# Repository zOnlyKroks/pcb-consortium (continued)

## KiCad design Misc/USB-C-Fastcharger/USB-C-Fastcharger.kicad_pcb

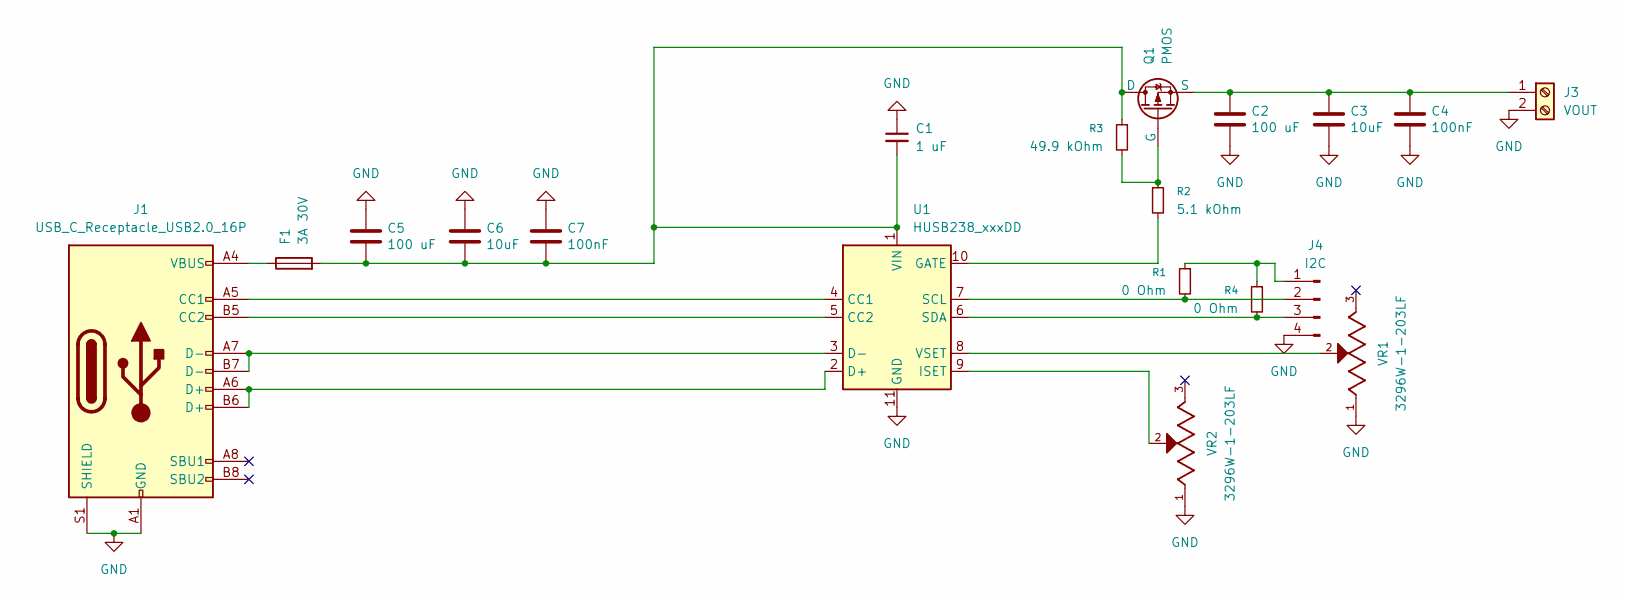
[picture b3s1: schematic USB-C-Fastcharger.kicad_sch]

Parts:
C1: 1 uF; C_0805_2012Metric; LCSC Part # C28323
C2, C5: 100 uF; C_0805_2012Metric; LCSC C141660
C3, C6: 10uF; C_0805_2012Metric; LCSC C440198
C4, C7: 100nF; C_0805_2012Metric; LCSC C49678
F1: 3A 30V; Fuse_2920_7451Metric; LCSC Part # C7190311
J1: USB_C_Receptacle_USB2.0_16P; USB_C_Receptacle_HRO_TYPE-C-31-M-12
J3: VOUT; WJ500V-5.08-2P; LCSC Part # C8465
J4: I2C; PinHeader_1x04_P2.54mm_Vertical; LCSC Part # C2691448
Q1: PMOS; SOT-23; LCSC Part # C150724
R1, R4: 0 Ohm; R_0805_2012Metric; LCSC Part # C17477
R2: 5.1 kOhm; R_0805_2012Metric; LCSC Part # C27834
R3: 49.9 kOhm; R_0805_2012Metric; LCSC Part # C5123618
U1: HUSB238_xxxDD; WDFN-10-1EP_3x3mm_P0.5mm_EP1.8x2.5mm
VR1, VR2: 3296W-1-203LF; TRIM_3296W-1-103LF; PARTREV 05/16; LCSC Part # C49190459

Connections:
GND: C1.1, C2.2, C3.2, C4.2, C5.1, C6.1, C7.1, J1.A1 (GND), J1.A12 (GND), J1.B1 (GND), J1.B12 (GND), J1.S1 (SHIELD), J3.2, J4.4, U1.11 (GND), VR1.1, VR2.1
unnamed: F1.1, J1.A4 (VBUS), J1.A9 (VBUS), J1.B4 (VBUS), J1.B9 (VBUS)
unnamed: J1.A5 (CC1), U1.4 (CC1)
unnamed: J1.B5 (CC2), U1.5 (CC2)
unnamed: C2.1, C3.1, C4.1, J3.1, Q1.3 (S)
unnamed: J4.1, R1.1, R4.1
unnamed: J4.2, R1.2, U1.7 (SCL)
unnamed: J4.3, R4.2, U1.6 (SDA)
unnamed: C1.2, C5.2, C6.2, C7.2, F1.2, Q1.1 (D), R3.1, U1.1 (VIN)
unnamed: Q1.2 (G), R2.1, R3.2
unnamed: J1.A6 (D+), J1.B6 (D+), U1.2 (D+)
unnamed: J1.A7 (D-), J1.B7 (D-), U1.3 (D-)
unnamed: R2.2, U1.10 (GATE)
unnamed: U1.9 (ISET), VR2.2
unnamed: U1.8 (VSET), VR1.2

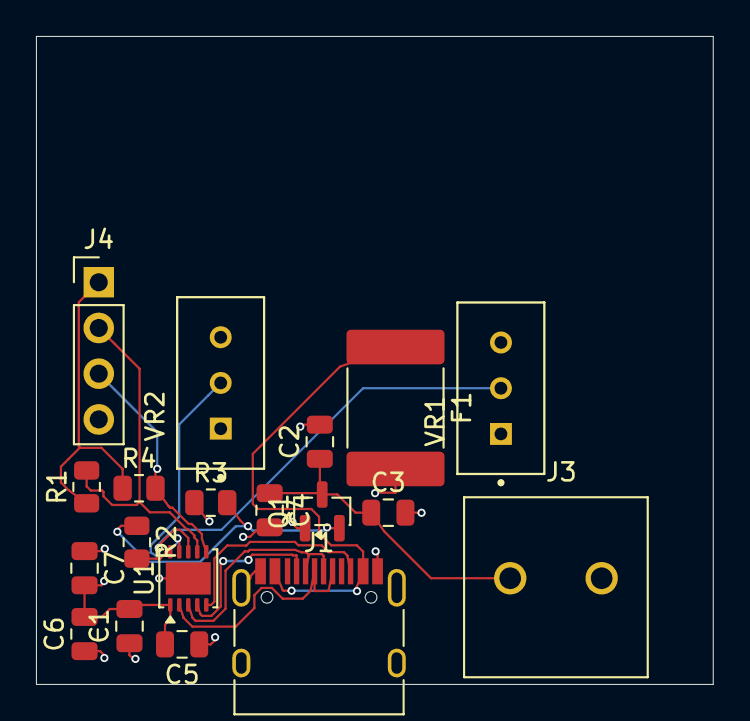
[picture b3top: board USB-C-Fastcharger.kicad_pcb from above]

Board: 4 copper layers, 37.6 x 36.0 mm, 19 parts (0 on the bottom side), 15 nets.

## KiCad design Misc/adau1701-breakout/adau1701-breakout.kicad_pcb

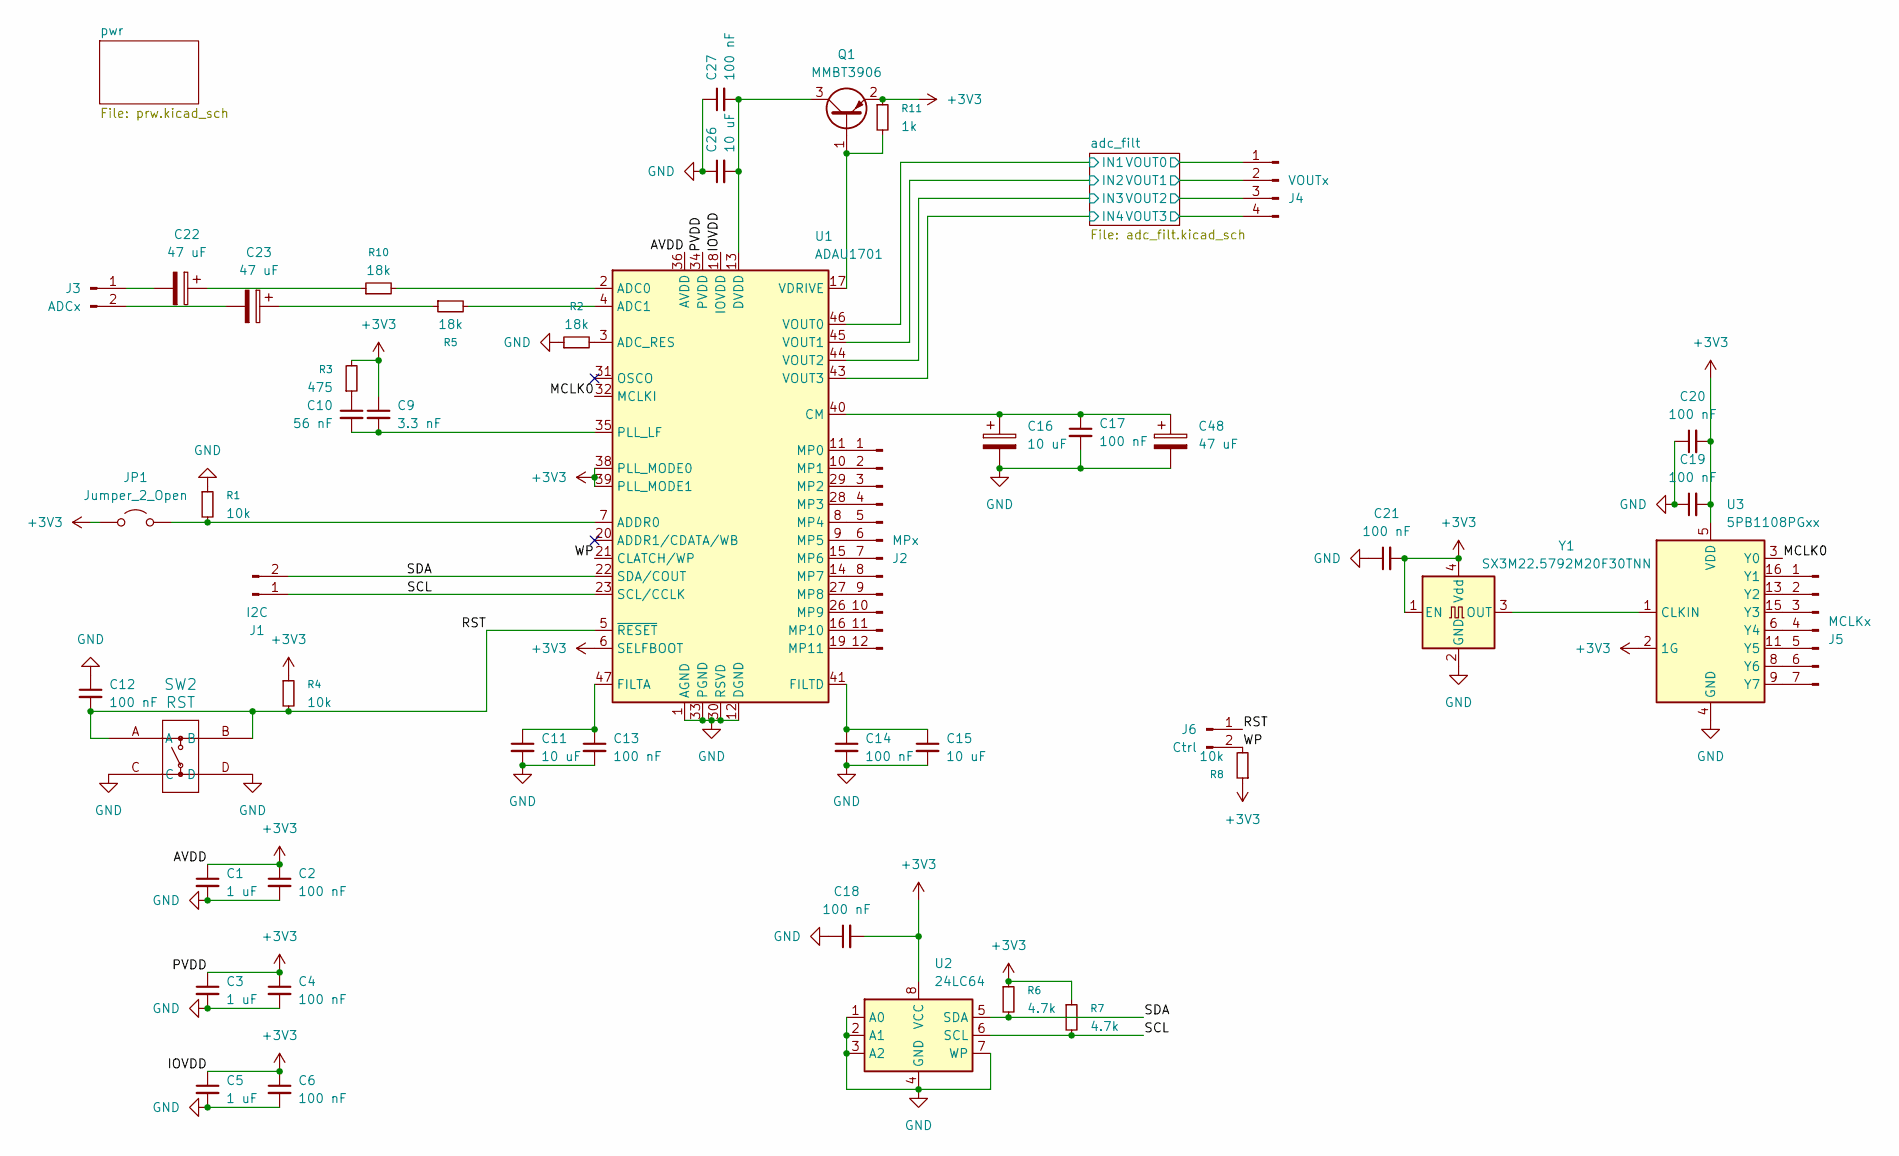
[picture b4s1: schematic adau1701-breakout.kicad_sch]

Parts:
C1, C3, C5: 1 uF; C_0603_1608Metric
C2, C4, C6, C12, C13, C14, C17, C18, C19, C20, C21, C27: 100 nF; C_0603_1608Metric
C9: 3.3 nF; C_0603_1608Metric
C10: 56 nF; C_0603_1608Metric
C11, C15, C16, C26: 10 uF; C_0603_1608Metric
C22, C23, C48: 47 uF; CP_Elec_6.3x5.4
J1: I2C; PinHeader_1x02_P2.54mm_Vertical
J2: MPx; PinHeader_1x12_P2.54mm_Vertical
J3: ADCx; PinHeader_1x02_P2.54mm_Vertical
J4: VOUTx; PinHeader_1x04_P2.54mm_Vertical
J5: MCLKx; PinHeader_1x07_P2.54mm_Vertical
J6: Ctrl; PinHeader_1x02_P2.54mm_Vertical
JP1: Jumper_2_Open; SolderJumper-2_P1.3mm_Open_RoundedPad1.0x1.5mm
Q1: MMBT3906; SOT-23
R1, R4, R8: 10k; R_0603_1608Metric
R2, R5, R10: 18k; R_0603_1608Metric
R3: 475; R_0603_1608Metric
R6, R7: 4.7k; R_0603_1608Metric
R11: 1k; R_0603_1608Metric
SW2: RST; KH-6X6X5H-STM_SKE
U1: ADAU1701; LQFP-48_7x7mm_P0.5mm
U2: 24LC64; SOIC-8_3.9x4.9mm_P1.27mm
U3: 5PB1108PGxx; TSSOP-16_4.4x5mm_P0.65mm
Y1: SX3M22.5792M20F30TNN; Crystal_SMD_3225-4Pin_3.2x2.5mm

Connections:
+3V3: C1.1, C2.1, C3.1, C4.1, C5.1, C6.1, C9.1, C18.2, C19.2, C20.2, C21.2, JP1.1 (A), Q1.2 (E), R3.2, R4.1, R6.1, R7.1, R8.1, R11.1, U1.6 (SELFBOOT), U1.18 (IOVDD), U1.34 (PVDD), U1.36 (AVDD), U1.38 (PLL_MODE0), U1.39 (PLL_MODE1), U1.48 (AVDD), U2.8 (VCC), U3.2 (1G), U3.5 (VDD), U3.10 (VDD), U3.14 (VDD), Y1.1 (EN), Y1.4 (Vdd); also elsewhere on the board
/MCLK0: U1.32 (MCLKI), U3.3 (Y0)
/RST: C12.2, J6.1, R4.2, SW2.A, SW2.B, U1.5 (~RESET)
/SCL: J1.1, R7.2, U1.23 (SCL/CCLK), U2.6 (SCL)
/SDA: J1.2, R6.2, U1.22 (SDA/COUT), U2.5 (SDA)
/WP: J6.2, R8.2, U1.21 (CLATCH/WP)
/adc_filt/IN1: U1.46 (VOUT0); also elsewhere on the board
/adc_filt/IN2: U1.45 (VOUT1); also elsewhere on the board
/adc_filt/IN3: U1.44 (VOUT2); also elsewhere on the board
/adc_filt/IN4: U1.43 (VOUT3); also elsewhere on the board
/adc_filt/VOUT0: J4.1; also elsewhere on the board
/adc_filt/VOUT1: J4.2; also elsewhere on the board
/adc_filt/VOUT2: J4.3; also elsewhere on the board
/adc_filt/VOUT3: J4.4; also elsewhere on the board
GND: C1.2, C2.2, C3.2, C4.2, C5.2, C6.2, C11.2, C12.1, C13.2, C14.2, C15.2, C16.2, C17.2, C18.1, C19.1, C20.1, C21.1, C26.1, C27.1, C48.2, R1.1, R2.1, SW2.C, SW2.D, U1.1 (AGND), U1.12 (DGND), U1.25 (DGND), U1.30 (RSVD), U1.33 (PGND), U1.37 (AGND), U1.42 (AGND), U2.1 (A0), U2.2 (A1), U2.3 (A2), U2.4 (GND), U2.7 (WP), U3.4 (GND), U3.7 (GND), U3.12 (GND), Y1.2 (GND); also elsewhere on the board
unnamed: C10.1, R3.1
unnamed: C22.1, R10.1
unnamed: C23.1, R5.1
unnamed: J2.1, U1.11 (MP0)
unnamed: J2.2, U1.10 (MP1)
unnamed: J2.3, U1.29 (MP2)
unnamed: J2.4, U1.28 (MP3)
unnamed: J2.5, U1.8 (MP4)
unnamed: J2.6, U1.9 (MP5)
unnamed: J2.7, U1.15 (MP6)
unnamed: J2.8, U1.14 (MP7)
unnamed: J2.9, U1.27 (MP8)
unnamed: J2.10, U1.26 (MP9)
unnamed: J2.11, U1.16 (MP10)
unnamed: J2.12, U1.19 (MP11)
unnamed: C22.2, J3.1
unnamed: C23.2, J3.2
unnamed: J5.1, U3.16 (Y1)
unnamed: J5.2, U3.13 (Y2)
unnamed: J5.3, U3.15 (Y3)
unnamed: J5.4, U3.6 (Y4)
unnamed: J5.5, U3.11 (Y5)
unnamed: J5.6, U3.8 (Y6)
unnamed: J5.7, U3.9 (Y7)
unnamed: JP1.2 (B), R1.2, U1.7 (ADDR0)
unnamed: Q1.1 (B), R11.2, U1.17 (VDRIVE)
unnamed: C26.2, C27.2, Q1.3 (C), U1.13 (DVDD), U1.24 (DVDD)
unnamed: R10.2, U1.2 (ADC0)
unnamed: R5.2, U1.4 (ADC1)
unnamed: R2.2, U1.3 (ADC_RES)
unnamed: C16.1, C17.1, C48.1, U1.40 (CM)
unnamed: C11.1, C13.1, U1.47 (FILTA)
unnamed: C14.1, C15.1, U1.41 (FILTD)
unnamed: C9.2, C10.2, U1.35 (PLL_LF)
unnamed: U3.1 (CLKIN), Y1.3 (OUT)

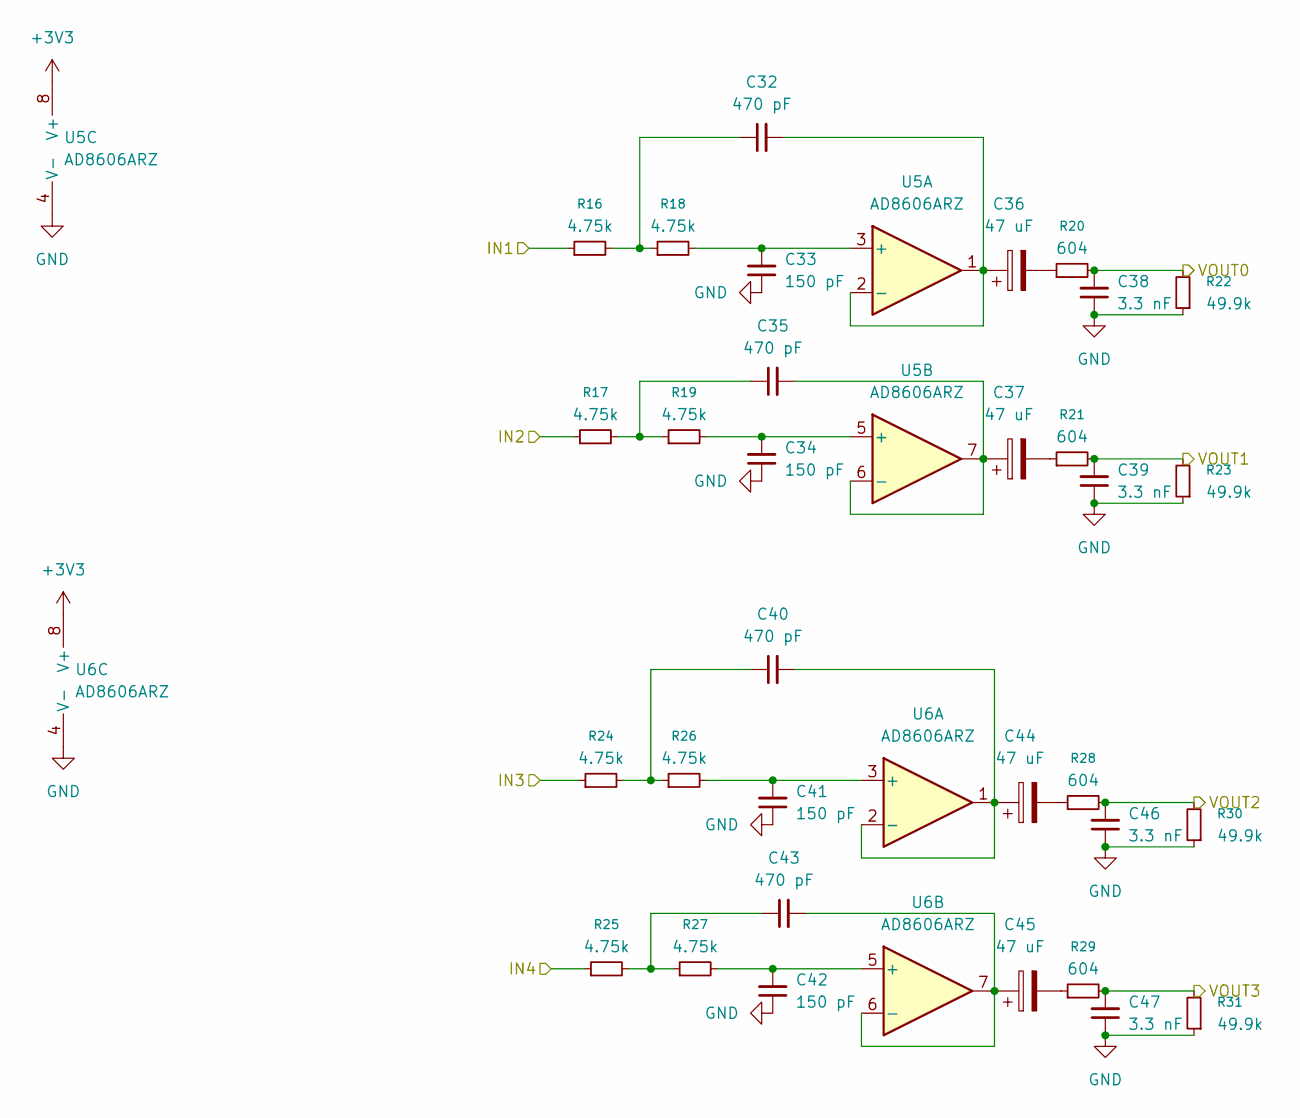
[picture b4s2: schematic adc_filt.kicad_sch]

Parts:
C32, C35, C40, C43: 470 pF; C_0603_1608Metric
C33, C34, C41, C42: 150 pF; C_0603_1608Metric
C36, C37, C44, C45: 47 uF; CP_Elec_6.3x5.4
C38, C39, C46, C47: 3.3 nF; C_0603_1608Metric
R16, R17, R18, R19, R24, R25, R26, R27: 4.75k; R_0603_1608Metric
R20, R21, R28, R29: 604; R_0603_1608Metric
R22, R23, R30, R31: 49.9k; R_0603_1608Metric
U5, U6: AD8606ARZ; SOIC-8_3.9x4.9mm_P1.27mm

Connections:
+3V3: U5.8 (V+), U6.8 (V+); also elsewhere on the board
/adc_filt/IN1: R16.1; also elsewhere on the board
/adc_filt/IN2: R17.1; also elsewhere on the board
/adc_filt/IN3: R24.1; also elsewhere on the board
/adc_filt/IN4: R25.1; also elsewhere on the board
/adc_filt/VOUT0: C38.2, R20.2, R22.2; also elsewhere on the board
/adc_filt/VOUT1: C39.2, R21.2, R23.2; also elsewhere on the board
/adc_filt/VOUT2: C46.2, R28.2, R30.2; also elsewhere on the board
/adc_filt/VOUT3: C47.2, R29.2, R31.2; also elsewhere on the board
GND: C33.1, C34.1, C38.1, C39.1, C41.1, C42.1, C46.1, C47.1, R22.1, R23.1, R30.1, R31.1, U5.4 (V-), U6.4 (V-); also elsewhere on the board
unnamed: C32.1, R16.2, R18.1
unnamed: C35.1, R17.2, R19.1
unnamed: C36.2, R20.1
unnamed: C37.2, R21.1
unnamed: C40.1, R24.2, R26.1
unnamed: C43.1, R25.2, R27.1
unnamed: C44.2, R28.1
unnamed: C45.2, R29.1
unnamed: C33.2, R18.2, U5.3 (+)
unnamed: C32.2, C36.1, U5.1, U5.2 (-)
unnamed: C34.2, R19.2, U5.5 (+)
unnamed: C35.2, C37.1, U5.6 (-), U5.7
unnamed: C41.2, R26.2, U6.3 (+)
unnamed: C40.2, C44.1, U6.1, U6.2 (-)
unnamed: C42.2, R27.2, U6.5 (+)
unnamed: C43.2, C45.1, U6.6 (-), U6.7

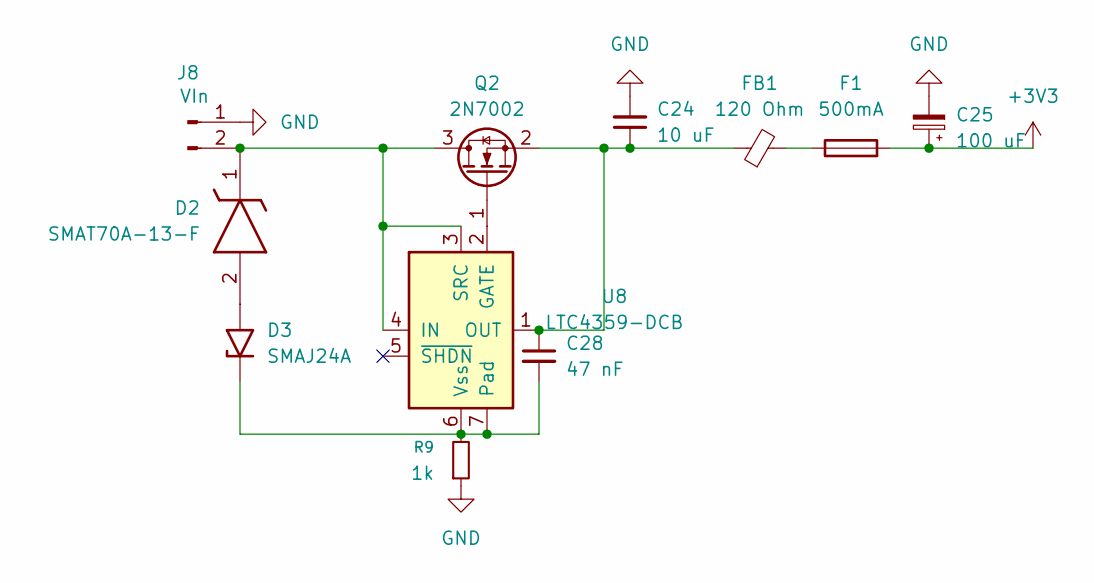
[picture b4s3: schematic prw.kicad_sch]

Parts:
C24: 10 uF; C_0805_2012Metric
C25: 100 uF; CP_EIA-3216-18_Kemet-A
C28: 47 nF; C_0603_1608Metric
D2: SMAT70A-13-F; DIOM5226X230N; Mouser Part Number 621-SMAT70A-13-F
D3: SMAJ24A; D_SMA
F1: 500mA; Fuse_0805_2012Metric
FB1: 120 Ohm; R_0402_1005Metric
J8: VIn; PinHeader_1x02_P2.54mm_Vertical
Q2: 2N7002; SOT-23
R9: 1k; R_0603_1608Metric
U8: LTC4359-DCB; DFN-6-1EP_3x2mm_P0.5mm_EP1.65x1.35mm

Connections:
+3V3: C25.1, F1.2; also elsewhere on the board
GND: C24.2, C25.2, J8.1, R9.1; also elsewhere on the board
unnamed: D2.2 (A), D3.2 (A2)
unnamed: D2.1 (K), J8.2, Q2.3 (D), U8.3 (SRC), U8.4 (IN)
unnamed: C28.2, D3.1 (A1), R9.2, U8.6 (Vss), U8.7 (Pad)
unnamed: F1.1, FB1.2
unnamed: Q2.1 (G), U8.2 (GATE)
unnamed: C24.1, C28.1, FB1.1, Q2.2 (S), U8.1 (OUT)

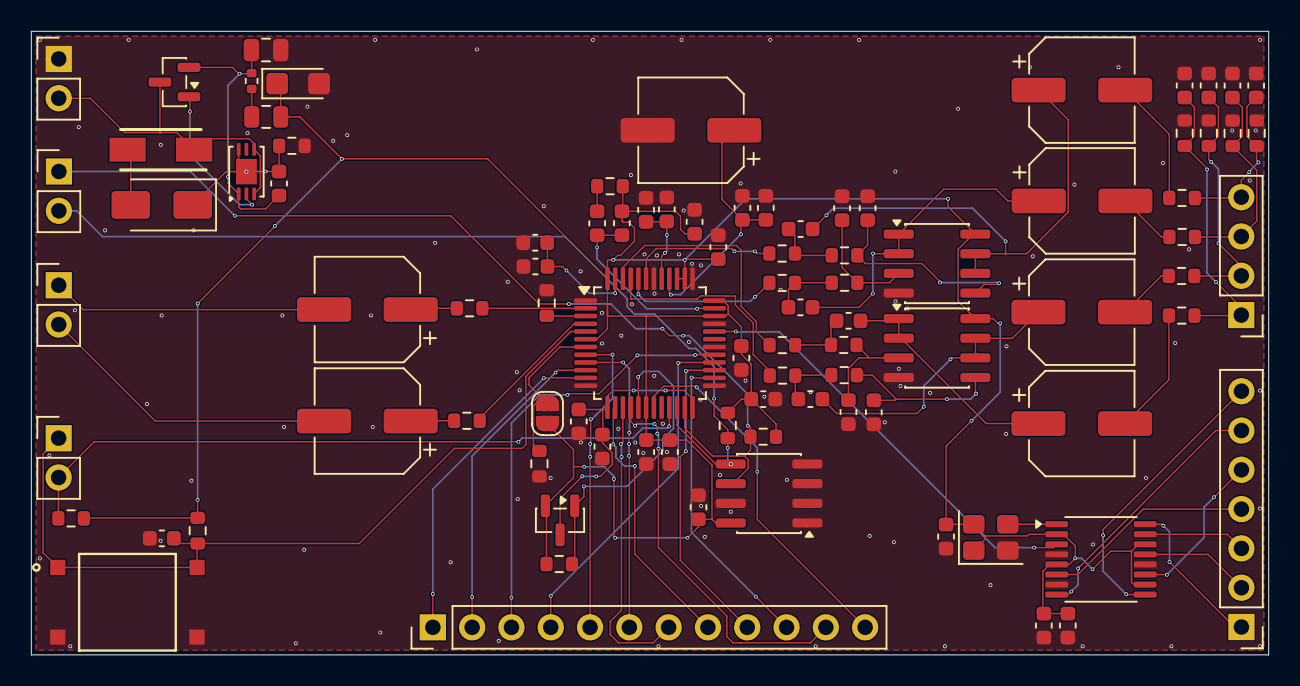
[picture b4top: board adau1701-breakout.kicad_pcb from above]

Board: 2 copper layers, 80.0 x 40.3 mm, 92 parts (0 on the bottom side), 72 nets.

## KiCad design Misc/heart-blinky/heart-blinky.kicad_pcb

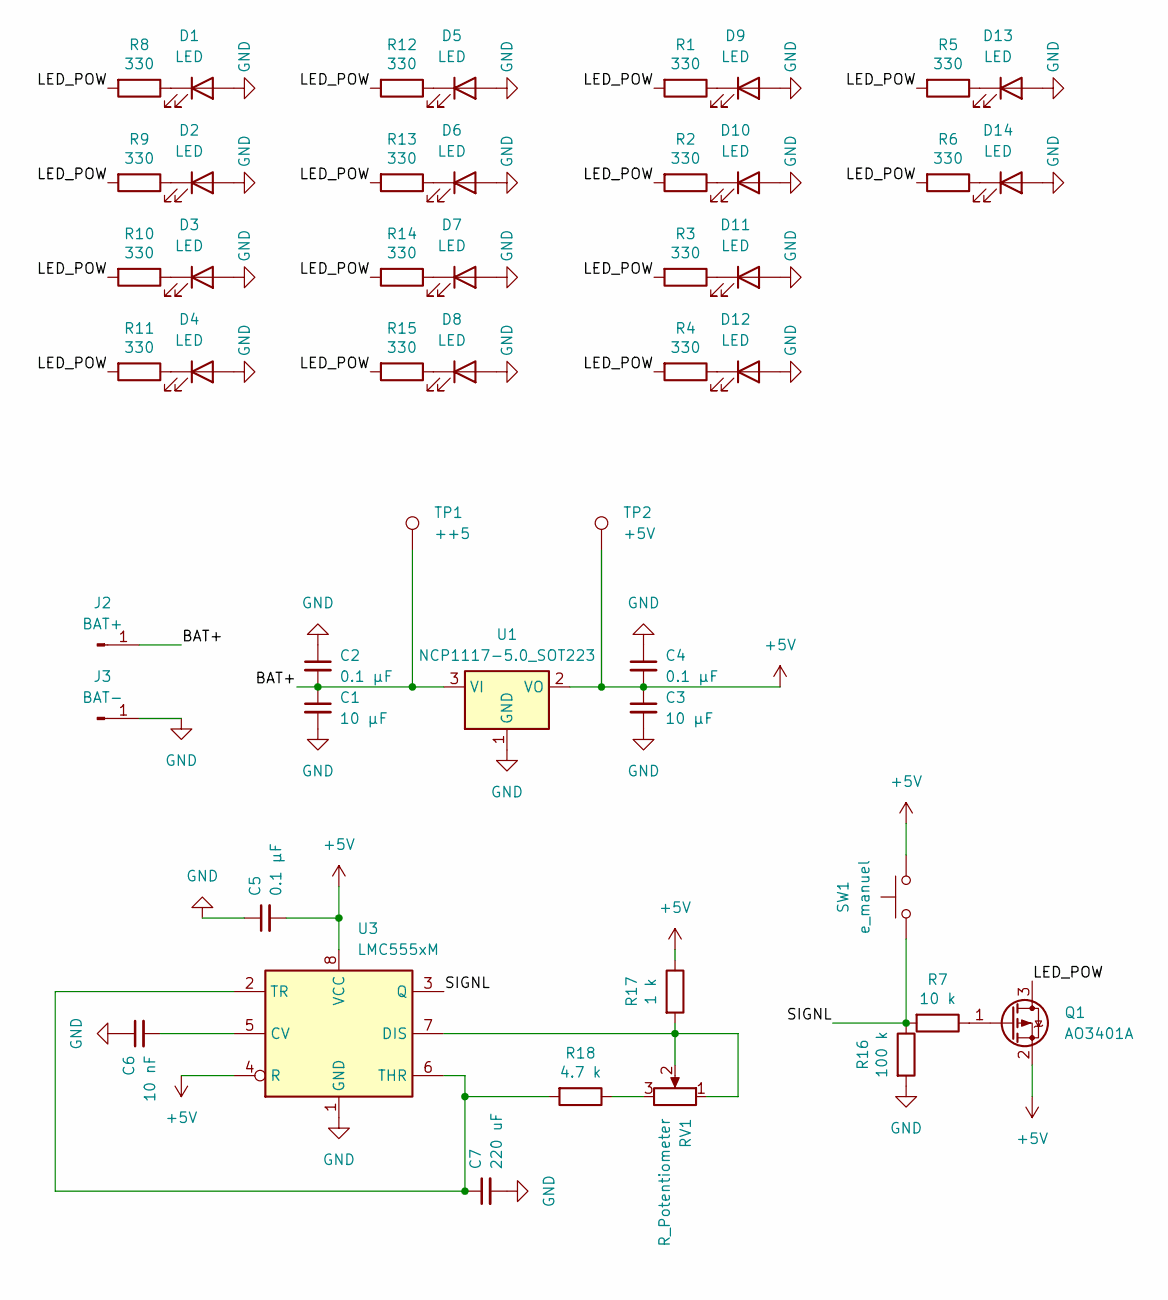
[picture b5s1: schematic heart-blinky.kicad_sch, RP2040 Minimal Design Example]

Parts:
C1, C3: 10 µF; C_0805_2012Metric
C2, C4, C5: 0.1 µF; C_0805_2012Metric
C6: 10 nF; C_0805_2012Metric
C7: 220 uF; CP_Elec_6.3x5.4
D1, D2, D3, D4, D5, D6, D7, D8, D9, D10, D11, D12, D13, D14: LED; LED_0805_2012Metric
J2: BAT+; SolderWirePad_1x01_SMD_1x2mm
J3: BAT-; SolderWirePad_1x01_SMD_1x2mm
Q1: AO3401A; SOT-23
R1, R2, R3, R4, R5, R6, R8, R9, R10, R11, R12, R13, R14, R15: 330; R_0805_2012Metric
R7: 10 k; R_0805_2012Metric
R16: 100 k; R_0805_2012Metric
R17: 1 k; R_0805_2012Metric
R18: 4.7 k; R_0805_2012Metric
RV1: R_Potentiometer; Potentiometer_Bourns_3314J_Vertical
SW1: e_manuel; SW_Push_1TS009xxxx-xxxx-xxxx_6x6x5mm; LCSC Part # C319410
TP1: ++5; TestPoint_Pad_1.5x1.5mm
TP2: +5V; TestPoint_Pad_1.5x1.5mm
U1: NCP1117-5.0_SOT223; SOT-223-3_TabPin2
U3: LMC555xM; SOIC-8_3.9x4.9mm_P1.27mm

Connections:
+5V: C3.1, C4.2, C5.2, Q1.2 (S), R17.1, SW1.2, TP2.1, U1.2 (VO), U3.4 (R), U3.8 (VCC)
/BAT+: C1.1, C2.2, J2.1, TP1.1, U1.3 (VI)
/LED_POW: Q1.3 (D), R1.2, R2.2, R3.2, R4.2, R5.2, R6.2, R8.2, R9.2, R10.2, R11.2, R12.2, R13.2, R14.2, R15.2
/SIGNL: R7.2, R16.1, SW1.1, U3.3 (Q)
GND: C1.2, C2.1, C3.2, C4.1, C5.1, C6.1, C7.2, D1.2 (A), D2.2 (A), D3.2 (A), D4.2 (A), D5.2 (A), D6.2 (A), D7.2 (A), D8.2 (A), D9.2 (A), D10.2 (A), D11.2 (A), D12.2 (A), D13.2 (A), D14.2 (A), J3.1, R16.2, U1.1 (GND), U3.1 (GND)
unnamed: D1.1 (K), R8.1
unnamed: D2.1 (K), R9.1
unnamed: D3.1 (K), R10.1
unnamed: D4.1 (K), R11.1
unnamed: D5.1 (K), R12.1
unnamed: D6.1 (K), R13.1
unnamed: D7.1 (K), R14.1
unnamed: D8.1 (K), R15.1
unnamed: D9.1 (K), R1.1
unnamed: D10.1 (K), R2.1
unnamed: D11.1 (K), R3.1
unnamed: D12.1 (K), R4.1
unnamed: D13.1 (K), R5.1
unnamed: D14.1 (K), R6.1
unnamed: Q1.1 (G), R7.1
unnamed: R18.1, RV1.3
unnamed: C6.2, U3.5 (CV)
unnamed: R17.2, RV1.1, RV1.2, U3.7 (DIS)
unnamed: C7.1, R18.2, U3.2 (TR), U3.6 (THR)

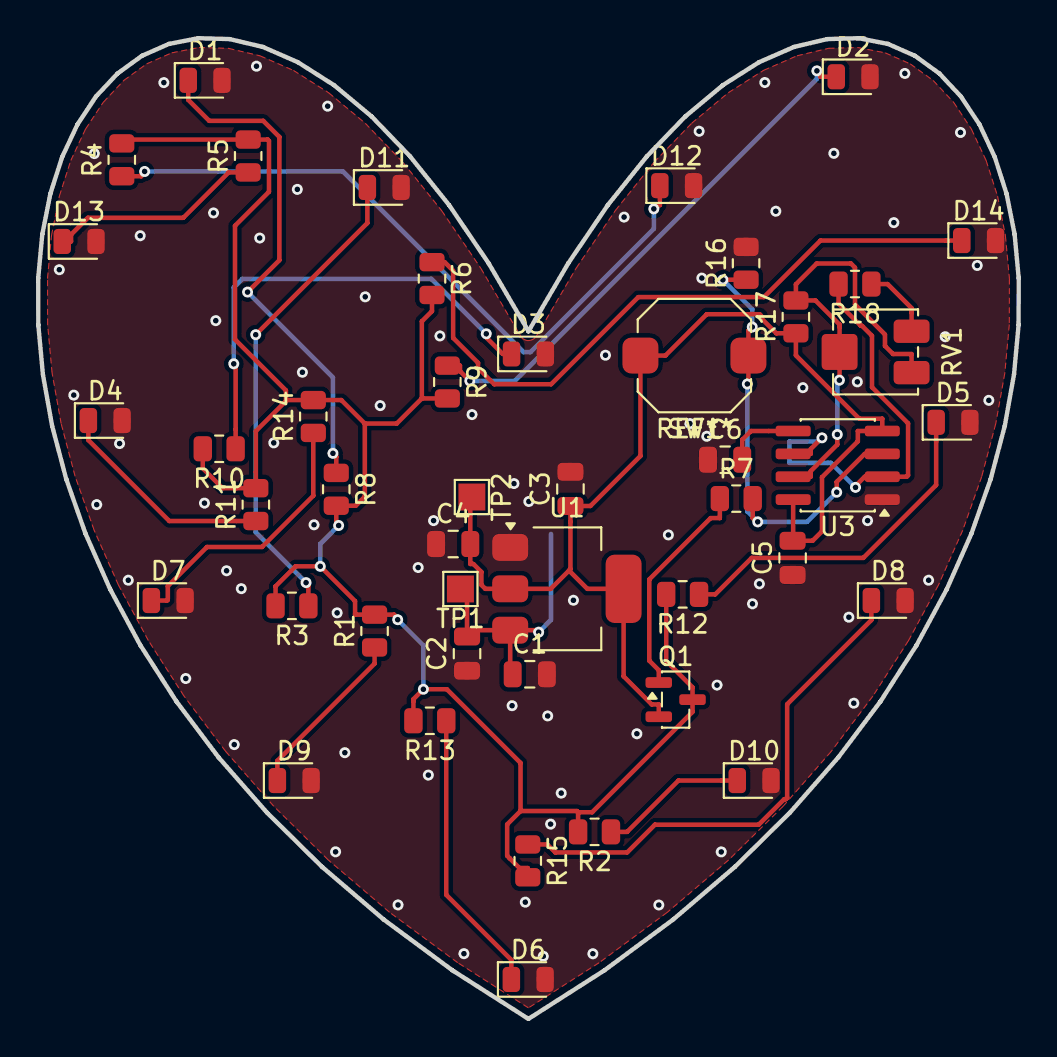
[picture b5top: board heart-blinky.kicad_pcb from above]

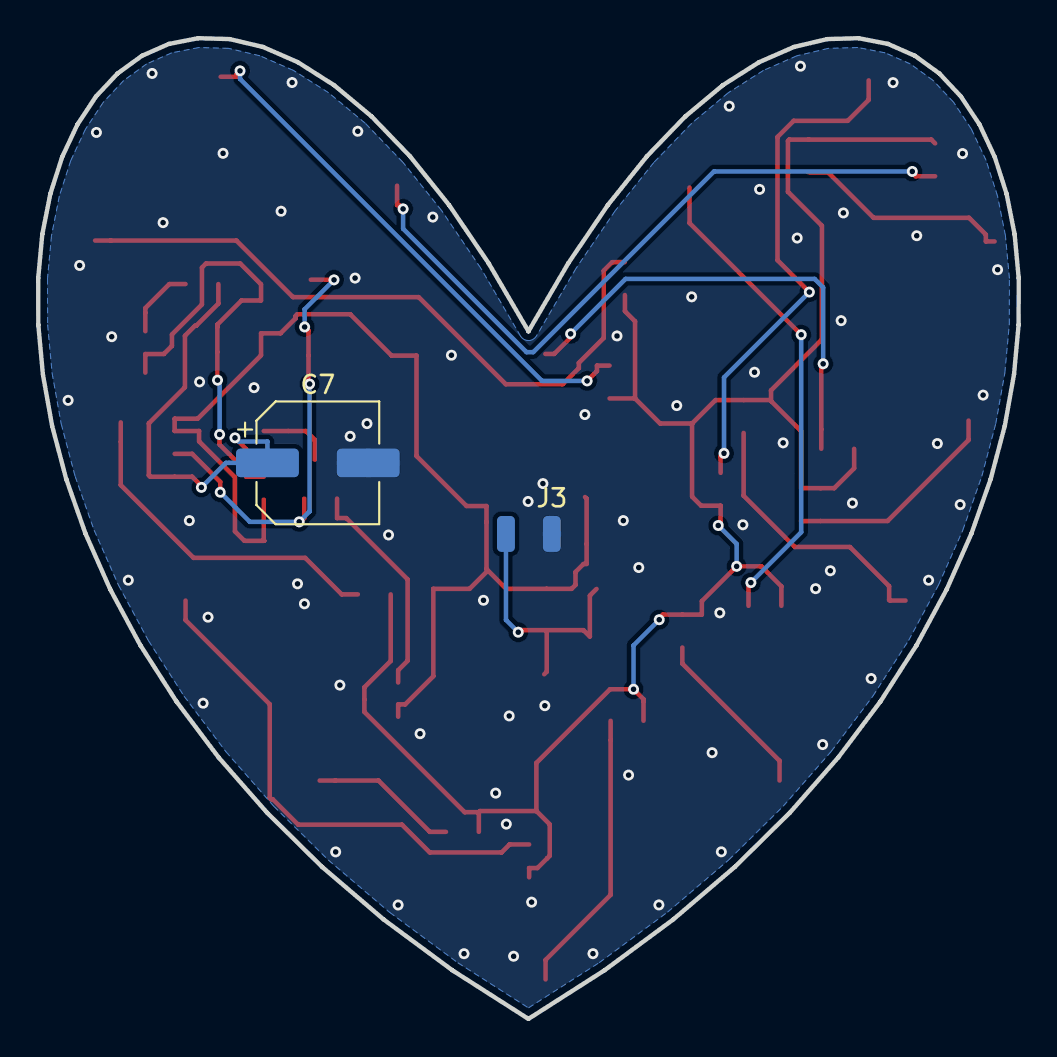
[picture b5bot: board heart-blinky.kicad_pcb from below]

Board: 2 copper layers, 54.5 x 54.5 mm, 48 parts (3 on the bottom side), 24 nets.

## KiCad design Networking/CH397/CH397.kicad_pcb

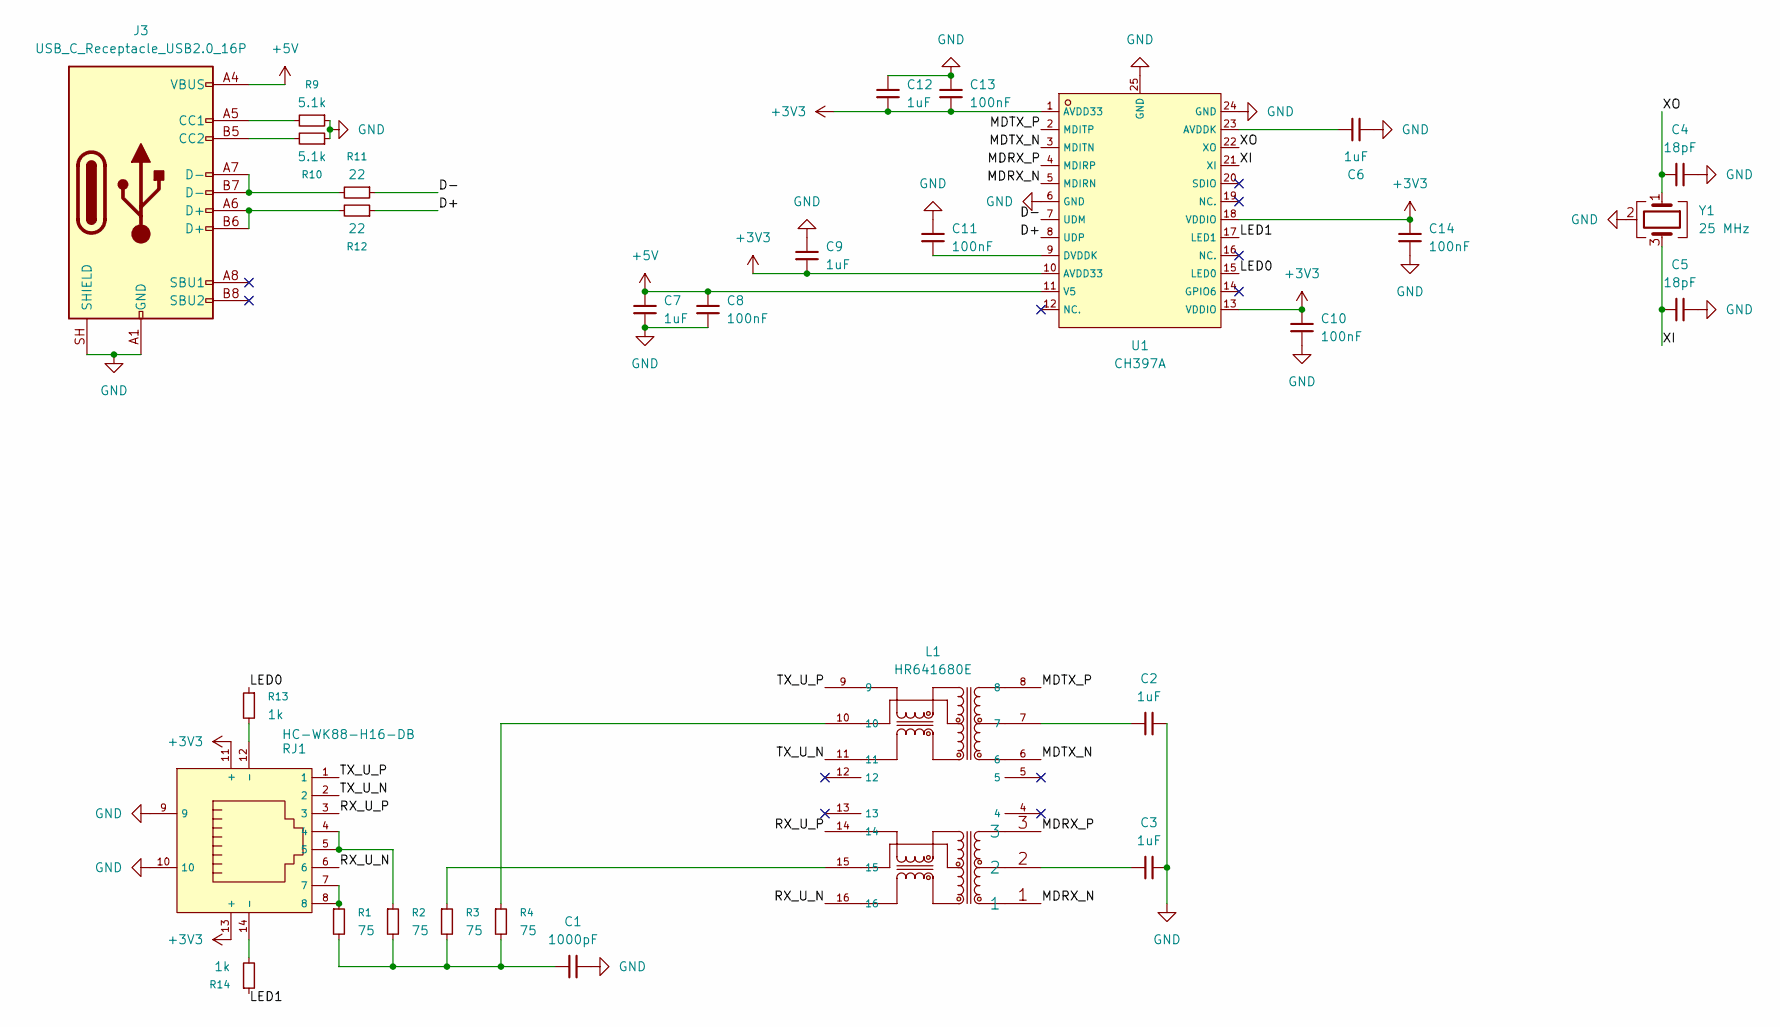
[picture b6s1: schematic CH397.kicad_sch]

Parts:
C1: 1000pF; C_0603_1608Metric
C2, C3, C6, C7, C9, C12: 1uF; C_0603_1608Metric
C4, C5: 18pF; C_0603_1608Metric
C8, C10, C11, C13, C14: 100nF; C_0603_1608Metric
J3: USB_C_Receptacle_USB2.0_16P; USB_C_Receptacle_HRO_TYPE-C-31-M-12
L1: HR641680E; C189555_XFMR-SMD_HR641680E; LCSC C189555
R1, R2, R3, R4: 75; R_0603_1608Metric
R9, R10: 5.1k; R_0603_1608Metric
R11, R12: 22; R_0603_1608Metric
R13, R14: 1k; R_0603_1608Metric
RJ1: HC-WK88-H16-DB; C7501824_RJ45-TH_HC-WK88-H16-DB; LCSC C7501824
U1: CH397A; C7465328_QFN-24_L4_0-W4_0-P0_50-BL-EP2_8; LCSC C7465328
Y1: 25 MHz; Crystal_SMD_3225-4Pin_3.2x2.5mm

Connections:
+3V3: C9.1, C10.1, C12.1, C13.1, C14.1, RJ1.11 (+), RJ1.13 (+), U1.1 (AVDD33), U1.10 (AVDD33), U1.13 (VDDIO), U1.18 (VDDIO)
+5V: C7.2, C8.2, J3.A4 (VBUS), J3.A9 (VBUS), J3.B4 (VBUS), J3.B9 (VBUS), U1.11 (V5)
/D+: R12.1, U1.8 (UDP)
/D-: R11.1, U1.7 (UDM)
/LED0: R13.1, U1.15 (LED0)
/LED1: R14.1, U1.17 (LED1)
/MDRX_N: L1.1, U1.5 (MDIRN)
/MDRX_P: L1.3, U1.4 (MDIRP)
/MDTX_N: L1.6, U1.3 (MDITN)
/MDTX_P: L1.8, U1.2 (MDITP)
/RX_U_N: L1.16, RJ1.6
/RX_U_P: L1.14, RJ1.3
/TX_U_N: L1.11, RJ1.2
/TX_U_P: L1.9, RJ1.1
/XI: C5.1, U1.21 (XI), Y1.3
/XO: C4.1, U1.22 (XO), Y1.1
GND: C1.2, C2.2, C3.2, C4.2, C5.2, C6.1, C7.1, C8.1, C9.2, C10.2, C11.2, C12.2, C13.2, C14.2, J3.A1 (GND), J3.A12 (GND), J3.B1 (GND), J3.B12 (GND), J3.SH (SHIELD), R9.1, R10.1, RJ1.9, RJ1.10, U1.6 (GND), U1.24 (GND), U1.25 (GND), Y1.2 (G), Y1.4 (G)
unnamed: C1.1, R1.2, R2.2, R3.2, R4.2
unnamed: C2.1, L1.7
unnamed: C3.1, L1.2
unnamed: J3.A5 (CC1), R9.2
unnamed: J3.B5 (CC2), R10.2
unnamed: J3.A6 (D+), J3.B6 (D+), R12.2
unnamed: J3.A7 (D-), J3.B7 (D-), R11.2
unnamed: L1.10, R4.1
unnamed: L1.15, R3.1
unnamed: R1.1, RJ1.7, RJ1.8
unnamed: R2.1, RJ1.4, RJ1.5
unnamed: R13.2, RJ1.12 (-)
unnamed: R14.2, RJ1.14 (-)
unnamed: C6.2, U1.23 (AVDDK)
unnamed: C11.1, U1.9 (DVDDK)

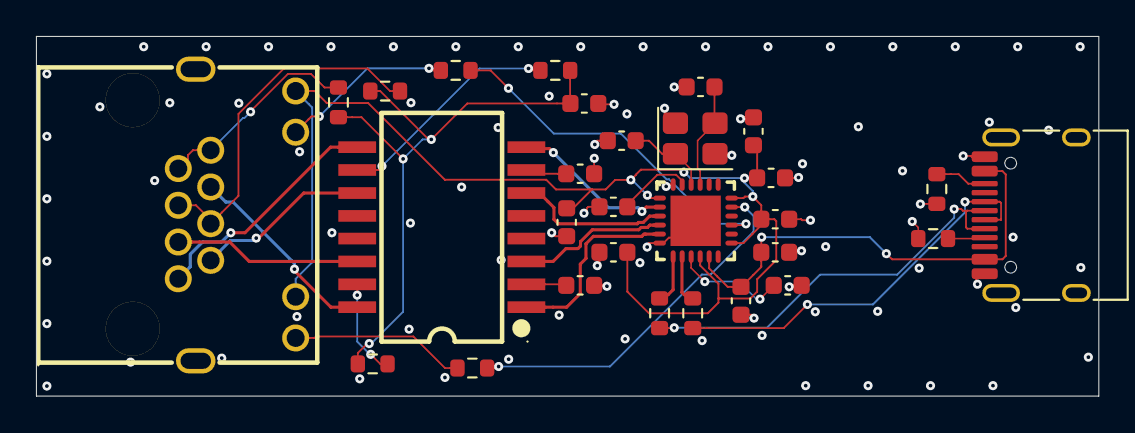
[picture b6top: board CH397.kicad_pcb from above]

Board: 4 copper layers, 59.0 x 20.0 mm, 29 parts (0 on the bottom side), 32 nets.

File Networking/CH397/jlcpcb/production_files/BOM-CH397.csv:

Comment,Designator,Footprint,LCSC,Quantity
1000pF,C1,C_0603_1608Metric,C1588,1
100nF,"C10,C11,C13,C14,C8",C_0603_1608Metric,C14663,5
18pF,"C4,C5",C_0603_1608Metric,C1647,2
1k,"R13,R14",R_0603_1608Metric,C21190,2
1uF,"C12,C2,C3,C6,C7,C9",C_0603_1608Metric,C15849,6
22,"R11,R12",R_0603_1608Metric,C23345,2
25 MHz,Y1,Crystal_SMD_3225-4Pin_3.2x2.5mm,C9006,1
5.1k,"R10,R9",R_0603_1608Metric,C23186,2
75,"R1,R2,R3,R4",R_0603_1608Metric,C4275,4
CH397A,U1,C7465328_QFN-24_L4_0-W4_0-P0_50-BL-EP2_8,C7465328,1
HC-WK88-H16-DB,RJ1,C7501824_RJ45-TH_HC-WK88-H16-DB,C7501824,1
HR641680E,L1,C189555_XFMR-SMD_HR641680E,C189555,1
USB_C_Receptacle_USB2.0_16P,J3,USB_C_Receptacle_HRO_TYPE-C-31-M-12,C165948,1
